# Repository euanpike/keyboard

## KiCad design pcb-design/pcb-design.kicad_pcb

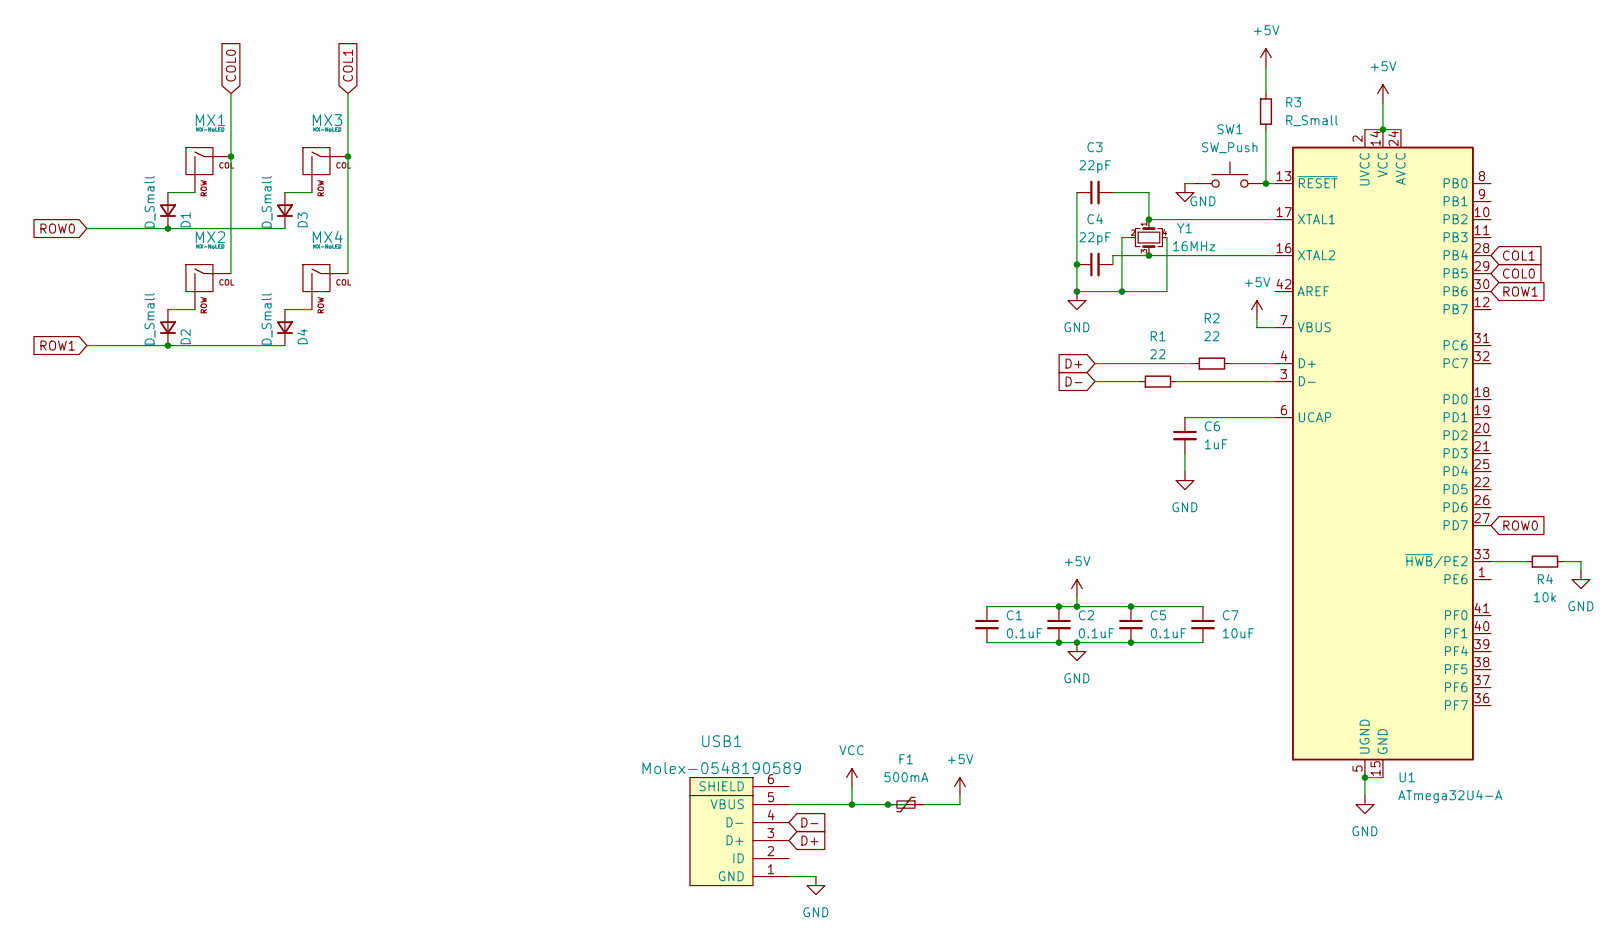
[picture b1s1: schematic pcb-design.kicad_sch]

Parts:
C1, C2, C5: 0.1uF; C_0805_2012Metric
C3, C4: 22pF; C_0805_2012Metric
C6: 1uF; C_0805_2012Metric
C7: 10uF; C_0805_2012Metric
D1, D2, D3, D4: D_Small; D_SOD-123
F1: 500mA; Fuse_1206_3216Metric
MX1, MX2, MX3, MX4: MX-NoLED; MX-1U-NoLED
R1, R2: 22; R_0805_2012Metric
R3: R_Small; R_0805_2012Metric
R4: 10k; R_0805_2012Metric
SW1: SW_Push; SKQG-1155865
U1: ATmega32U4-A; TQFP-44_10x10mm_P0.8mm
USB1: Molex-0548190589
Y1: 16MHz; Crystal_SMD_3225-4Pin_3.2x2.5mm

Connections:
+5V: C1.1, C2.1, C5.1, C7.1, F1.1, R3.1, U1.2 (UVCC), U1.7 (VBUS), U1.14 (VCC), U1.24 (AVCC), U1.34 (VCC), U1.44 (AVCC)
COL0: MX1.1 (COL), MX2.1 (COL), U1.29 (PB5)
COL1: MX3.1 (COL), MX4.1 (COL), U1.28 (PB4)
D+: R2.1, USB1.3 (D+)
D-: R1.1, USB1.4 (D-)
GND: C1.2, C2.2, C3.1, C4.1, C5.2, C6.2, C7.2, R4.2, SW1.1, U1.5 (UGND), U1.15 (GND), U1.23 (GND), U1.35 (GND), U1.43 (GND), USB1.1 (GND), Y1.2, Y1.4
unnamed: C3.2, U1.17 (XTAL1), Y1.1
unnamed: C4.2, U1.16 (XTAL2), Y1.3
unnamed: C6.1, U1.6 (UCAP)
unnamed: D1.2 (A), MX1.2 (ROW)
unnamed: D2.2 (A), MX2.2 (ROW)
unnamed: D3.2 (A), MX3.2 (ROW)
unnamed: D4.2 (A), MX4.2 (ROW)
unnamed: R1.2, U1.3 (D-)
unnamed: R2.2, U1.4 (D+)
unnamed: R3.2, SW1.2, U1.13 (~RESET)
unnamed: R4.1, U1.33 (~HWB/PE2)
ROW0: D1.1 (K), D3.1 (K), U1.27 (PD7)
ROW1: D2.1 (K), D4.1 (K), U1.30 (PB6)
VCC: F1.2, USB1.5 (VBUS)

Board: 2 copper layers, 24 parts (0 on the bottom side), 20 nets, no tracks yet.

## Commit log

2022-01-05 created ki project
2022-01-05 Added submodules
2022-01-05 added keyboard libraries
2022-01-06 created sch for 4 key keyboard
2022-01-06 started PCB placement
